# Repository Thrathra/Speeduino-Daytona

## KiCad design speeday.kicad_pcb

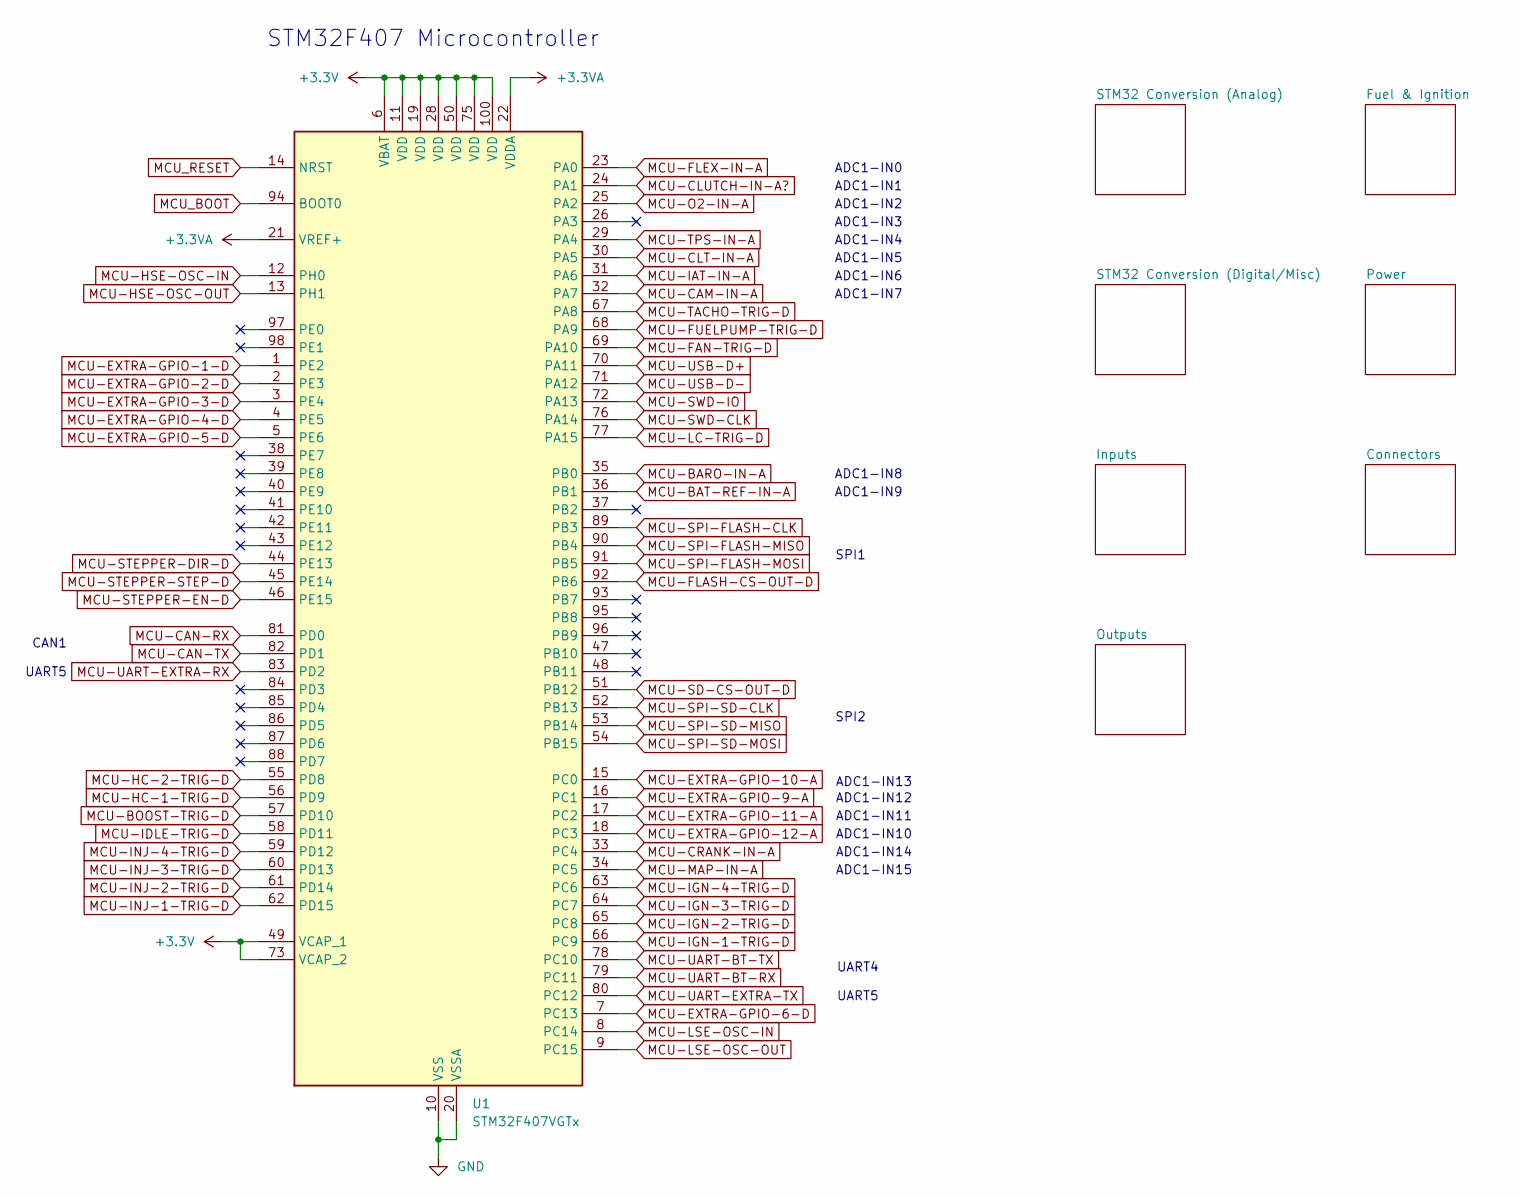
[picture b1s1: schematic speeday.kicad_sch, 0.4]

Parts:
U1: STM32F407VGTx; LQFP-100_14x14mm_P0.5mm

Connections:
+3.3V: U1.6 (VBAT), U1.11 (VDD), U1.19 (VDD), U1.28 (VDD), U1.49 (VCAP_1), U1.50 (VDD), U1.73 (VCAP_2), U1.75 (VDD), U1.100 (VDD); also elsewhere on the board
+3.3VA: U1.21 (VREF+), U1.22 (VDDA); also elsewhere on the board
GND: U1.10 (VSS), U1.20 (VSSA), U1.27 (VSS), U1.74 (VSS), U1.99 (VSS); also elsewhere on the board
MCU-BARO-IN-A: U1.35 (PB0); also elsewhere on the board
MCU-BAT-REF-IN-A: U1.36 (PB1); also elsewhere on the board
MCU-BOOST-TRIG-D: U1.57 (PD10); also elsewhere on the board
MCU-CAM-IN-A: U1.32 (PA7); also elsewhere on the board
MCU-CAN-RX: U1.81 (PD0); also elsewhere on the board
MCU-CAN-TX: U1.82 (PD1); also elsewhere on the board
MCU-CLT-IN-A: U1.30 (PA5); also elsewhere on the board
MCU-CLUTCH-IN-A?: U1.24 (PA1); also elsewhere on the board
MCU-CRANK-IN-A: U1.33 (PC4); also elsewhere on the board
MCU-EXTRA-GPIO-1-D: U1.1 (PE2); also elsewhere on the board
MCU-EXTRA-GPIO-2-D: U1.2 (PE3); also elsewhere on the board
MCU-EXTRA-GPIO-3-D: U1.3 (PE4); also elsewhere on the board
MCU-EXTRA-GPIO-4-D: U1.4 (PE5); also elsewhere on the board
MCU-EXTRA-GPIO-5-D: U1.5 (PE6); also elsewhere on the board
MCU-EXTRA-GPIO-6-D: U1.7 (PC13); also elsewhere on the board
MCU-EXTRA-GPIO-9-A: U1.16 (PC1); also elsewhere on the board
MCU-EXTRA-GPIO-10-A: U1.15 (PC0); also elsewhere on the board
MCU-EXTRA-GPIO-11-A: U1.17 (PC2); also elsewhere on the board
MCU-EXTRA-GPIO-12-A: U1.18 (PC3); also elsewhere on the board
MCU-FAN-TRIG-D: U1.69 (PA10); also elsewhere on the board
MCU-FLASH-CS-OUT-D: U1.92 (PB6); also elsewhere on the board
MCU-FLEX-IN-A: U1.23 (PA0); also elsewhere on the board
MCU-FUELPUMP-TRIG-D: U1.68 (PA9); also elsewhere on the board
MCU-HC-1-TRIG-D: U1.56 (PD9); also elsewhere on the board
MCU-HC-2-TRIG-D: U1.55 (PD8); also elsewhere on the board
MCU-HSE-OSC-IN: U1.12 (PH0); also elsewhere on the board
MCU-HSE-OSC-OUT: U1.13 (PH1); also elsewhere on the board
MCU-IAT-IN-A: U1.31 (PA6); also elsewhere on the board
MCU-IDLE-TRIG-D: U1.58 (PD11); also elsewhere on the board
MCU-IGN-1-TRIG-D: U1.66 (PC9); also elsewhere on the board
MCU-IGN-2-TRIG-D: U1.65 (PC8); also elsewhere on the board
MCU-IGN-3-TRIG-D: U1.64 (PC7); also elsewhere on the board
MCU-IGN-4-TRIG-D: U1.63 (PC6); also elsewhere on the board
MCU-INJ-1-TRIG-D: U1.62 (PD15); also elsewhere on the board
MCU-INJ-2-TRIG-D: U1.61 (PD14); also elsewhere on the board
MCU-INJ-3-TRIG-D: U1.60 (PD13); also elsewhere on the board
MCU-INJ-4-TRIG-D: U1.59 (PD12); also elsewhere on the board
MCU-LC-TRIG-D: U1.77 (PA15); also elsewhere on the board
MCU-LSE-OSC-IN: U1.8 (PC14); also elsewhere on the board
MCU-LSE-OSC-OUT: U1.9 (PC15); also elsewhere on the board
MCU-MAP-IN-A: U1.34 (PC5); also elsewhere on the board
MCU-O2-IN-A: U1.25 (PA2); also elsewhere on the board
MCU-SD-CS-OUT-D: U1.51 (PB12); also elsewhere on the board
MCU-SPI-FLASH-CLK: U1.89 (PB3); also elsewhere on the board
MCU-SPI-FLASH-MISO: U1.90 (PB4); also elsewhere on the board
MCU-SPI-FLASH-MOSI: U1.91 (PB5); also elsewhere on the board
MCU-SPI-SD-CLK: U1.52 (PB13); also elsewhere on the board
MCU-SPI-SD-MISO: U1.53 (PB14); also elsewhere on the board
MCU-SPI-SD-MOSI: U1.54 (PB15); also elsewhere on the board
MCU-STEPPER-DIR-D: U1.44 (PE13); also elsewhere on the board
MCU-STEPPER-EN-D: U1.46 (PE15); also elsewhere on the board
MCU-STEPPER-STEP-D: U1.45 (PE14); also elsewhere on the board
MCU-SWD-CLK: U1.76 (PA14); also elsewhere on the board
MCU-SWD-IO: U1.72 (PA13); also elsewhere on the board
MCU-TACHO-TRIG-D: U1.67 (PA8); also elsewhere on the board
MCU-TPS-IN-A: U1.29 (PA4); also elsewhere on the board
MCU-UART-BT-RX: U1.79 (PC11); also elsewhere on the board
MCU-UART-BT-TX: U1.78 (PC10); also elsewhere on the board
MCU-UART-EXTRA-RX: U1.83 (PD2); also elsewhere on the board
MCU-UART-EXTRA-TX: U1.80 (PC12); also elsewhere on the board
MCU-USB-D+: U1.70 (PA11); also elsewhere on the board
MCU-USB-D-: U1.71 (PA12); also elsewhere on the board
MCU_BOOT: U1.94 (BOOT0); also elsewhere on the board
MCU_RESET: U1.14 (NRST); also elsewhere on the board

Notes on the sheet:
SPI1
ADC1-IN3
CAN1
ADC1-IN14
ADC1-IN2
ADC1-IN5
UART5
ADC1-IN9
ADC1-IN13
ADC1-IN10
SPI2
ADC1-IN15
ADC1-IN8
ADC1-IN0
STM32F407 Microcontroller
UART4
ADC1-IN4
ADC1-IN7
ADC1-IN1
ADC1-IN12
ADC1-IN11
ADC1-IN6

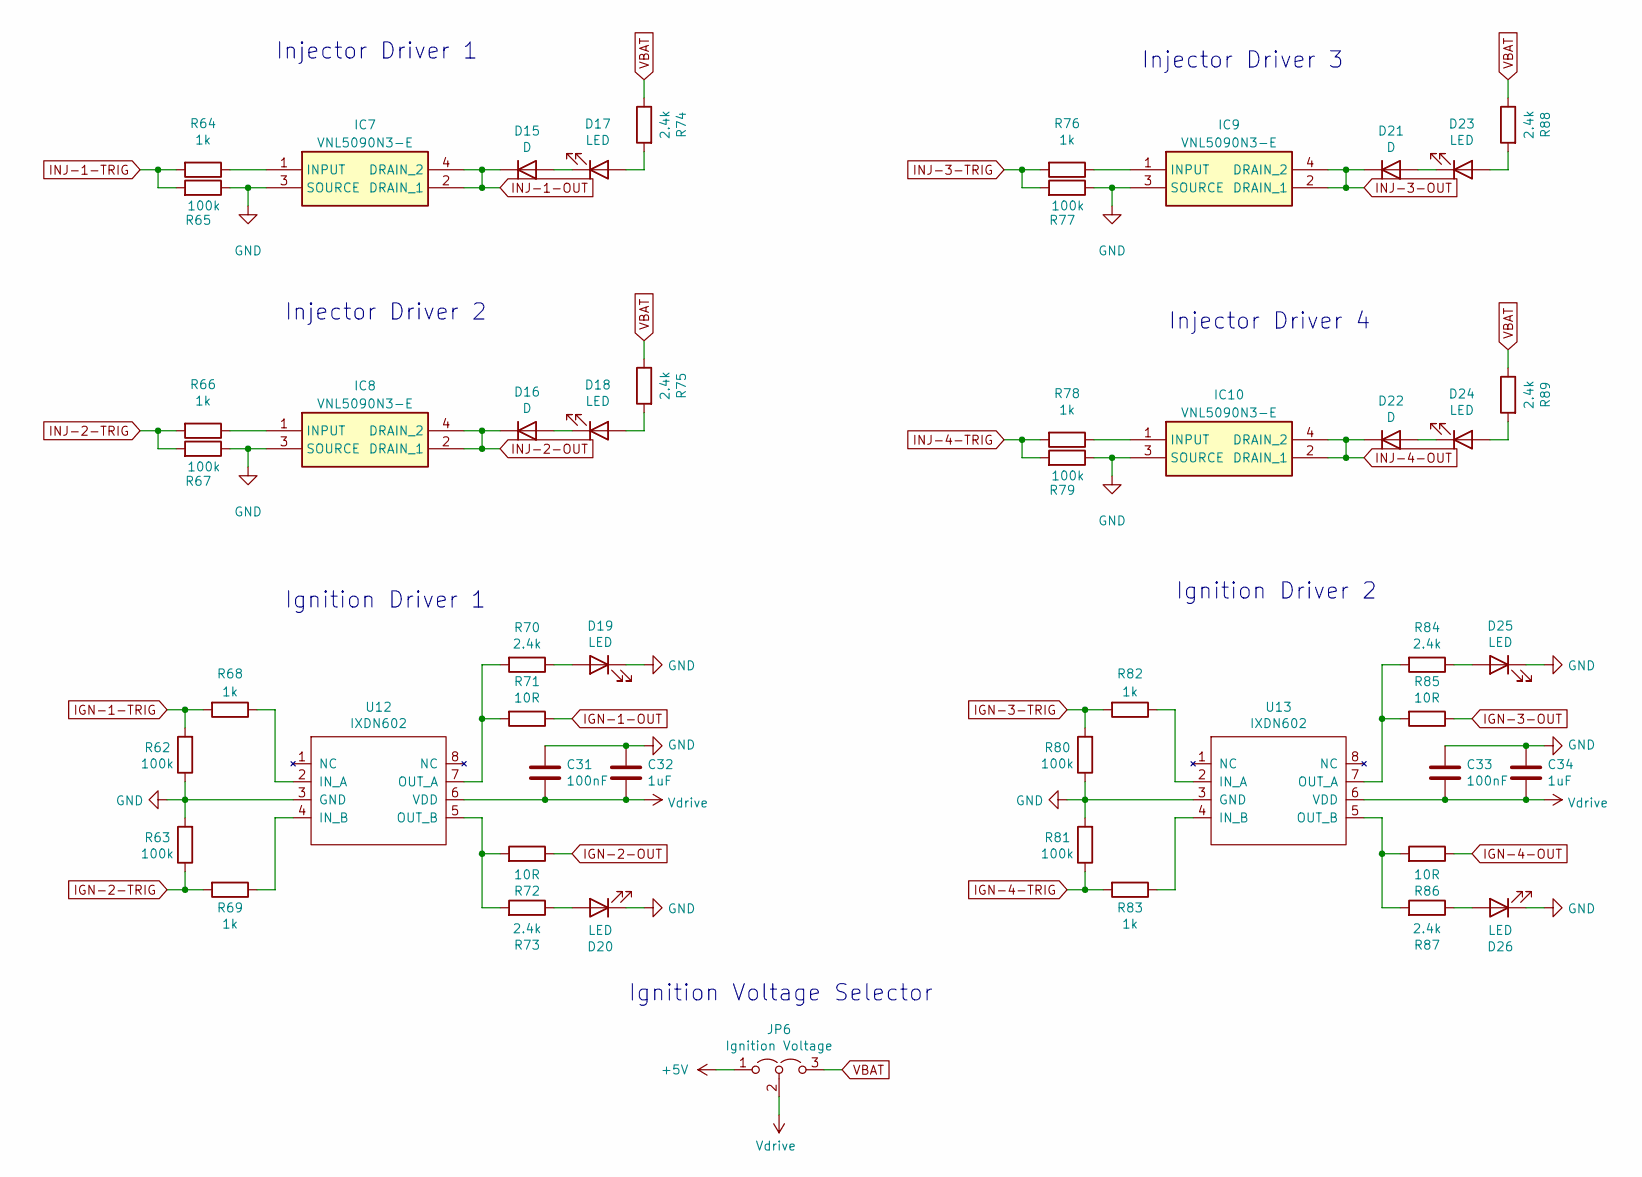
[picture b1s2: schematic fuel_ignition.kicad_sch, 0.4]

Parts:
C31, C33: 100nF; C_0805_2012Metric; Manufacturer_Part_Number CC0805KRX7R9BB104; Digikey Part Number 311-1140-1-ND
C32, C34: 1uF; C_0805_2012Metric; Manufacturer_Part_Number CC0805KKX7R7BB105; Digikey Part Number 311-1365-1-ND
D15, D16, D21, D22: D; D_SOD-323; Manufacturer_Part_Number 1N4448WX-TP; Digikey Part Number 1N4448WXTPMSCT-ND
D17, D18, D19, D20, D23, D24, D25, D26: LED; LED_0805_2012Metric; Manufacturer_Part_Number LH R974-LP-1; Digikey Part Number 475-1415-1-ND
IC7, IC8, IC9, IC10: VNL5090N3-E; SOT230P700X180-4N; Manufacturer_Part_Number VNL5090N3-E
JP6: Ignition Voltage; SolderJumper-3_P1.3mm_Open_RoundedPad1.0x1.5mm; Manufacturer_Part_Number M20-9990345; Digikey Part Number 952-2263-ND
R62, R63, R65, R67, R77, R79, R80, R81: 100k; R_0805_2012Metric; Manufacturer_Part_Number RC0805FR-07100KL; Digikey Part Number 311-100KCRCT-ND
R64, R66, R68, R69, R76, R78, R82, R83: 1k; R_0805_2012Metric; Manufacturer_Part_Number RC0805FR-071KL; Digikey Part Number 311-1.00KCRCT-ND
R70, R73, R74, R75, R84, R87, R88, R89: 2.4k; R_0805_2012Metric; Manufacturer_Part_Number RC0805FR-072K4L; Digikey Part Number 311-2.40KCRCT-ND
R71, R72, R85, R86: 10R; R_1206_3216Metric; Manufacturer_Part_Number RC1206FR-0710RL; Digikey Part Number 311-10.0FRCT-ND
U12, U13: IXDN602; SOIC-8_3.9x4.9mm_P1.27mm; Manufacturer_Part_Number IXDN602SIATR; Digikey Part Number 212-IXDN602SIACT-ND

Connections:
+5V: JP6.1 (A); also elsewhere on the board
GND: C31.1, C32.1, C33.1, C34.1, D19.1 (K), D20.1 (K), D25.1 (K), D26.1 (K), IC7.3 (SOURCE), IC8.3 (SOURCE), IC9.3 (SOURCE), IC10.3 (SOURCE), R62.1, R63.2, R65.1, R67.1, R77.1, R79.1, R80.1, R81.2, U12.3 (GND), U13.3 (GND); also elsewhere on the board
IGN-1-OUT: R71.1; also elsewhere on the board
IGN-1-TRIG: R62.2, R68.2; also elsewhere on the board
IGN-2-OUT: R72.1; also elsewhere on the board
IGN-2-TRIG: R63.1, R69.2; also elsewhere on the board
IGN-3-OUT: R85.1; also elsewhere on the board
IGN-3-TRIG: R80.2, R82.2; also elsewhere on the board
IGN-4-OUT: R86.1; also elsewhere on the board
IGN-4-TRIG: R81.1, R83.2; also elsewhere on the board
INJ-1-OUT: D15.1 (K), IC7.2 (DRAIN_1), IC7.4 (DRAIN_2); also elsewhere on the board
INJ-1-TRIG: R64.2, R65.2; also elsewhere on the board
INJ-2-OUT: D16.1 (K), IC8.2 (DRAIN_1), IC8.4 (DRAIN_2); also elsewhere on the board
INJ-2-TRIG: R66.2, R67.2; also elsewhere on the board
INJ-3-OUT: D21.1 (K), IC9.2 (DRAIN_1), IC9.4 (DRAIN_2); also elsewhere on the board
INJ-3-TRIG: R76.2, R77.2; also elsewhere on the board
INJ-4-OUT: D22.1 (K), IC10.2 (DRAIN_1), IC10.4 (DRAIN_2); also elsewhere on the board
INJ-4-TRIG: R78.2, R79.2; also elsewhere on the board
unnamed: D15.2 (A), D17.1 (K)
unnamed: D16.2 (A), D18.1 (K)
unnamed: D17.2 (A), R74.2
unnamed: D18.2 (A), R75.2
unnamed: D19.2 (A), R70.1
unnamed: D20.2 (A), R73.1
unnamed: D21.2 (A), D23.1 (K)
unnamed: D22.2 (A), D24.1 (K)
unnamed: D23.2 (A), R88.2
unnamed: D24.2 (A), R89.2
unnamed: D25.2 (A), R84.1
unnamed: D26.2 (A), R87.1
unnamed: IC7.1 (INPUT), R64.1
unnamed: IC8.1 (INPUT), R66.1
unnamed: IC9.1 (INPUT), R76.1
unnamed: IC10.1 (INPUT), R78.1
unnamed: R68.1, U12.2 (IN_A)
unnamed: R69.1, U12.4 (IN_B)
unnamed: R70.2, R71.2, U12.7 (OUT_A)
unnamed: R72.2, R73.2, U12.5 (OUT_B)
unnamed: R82.1, U13.2 (IN_A)
unnamed: R83.1, U13.4 (IN_B)
unnamed: R84.2, R85.2, U13.7 (OUT_A)
unnamed: R86.2, R87.2, U13.5 (OUT_B)
VBAT: JP6.3 (B), R74.1, R75.1, R88.1, R89.1; also elsewhere on the board
Vdrive: C31.2, C32.2, C33.2, C34.2, JP6.2 (C), U12.6 (VDD), U13.6 (VDD)

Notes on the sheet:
Ignition Voltage Selector
Injector Driver 4
Injector Driver 2
Ignition Driver 2
Injector Driver 1
Injector Driver 3
Ignition Driver 1

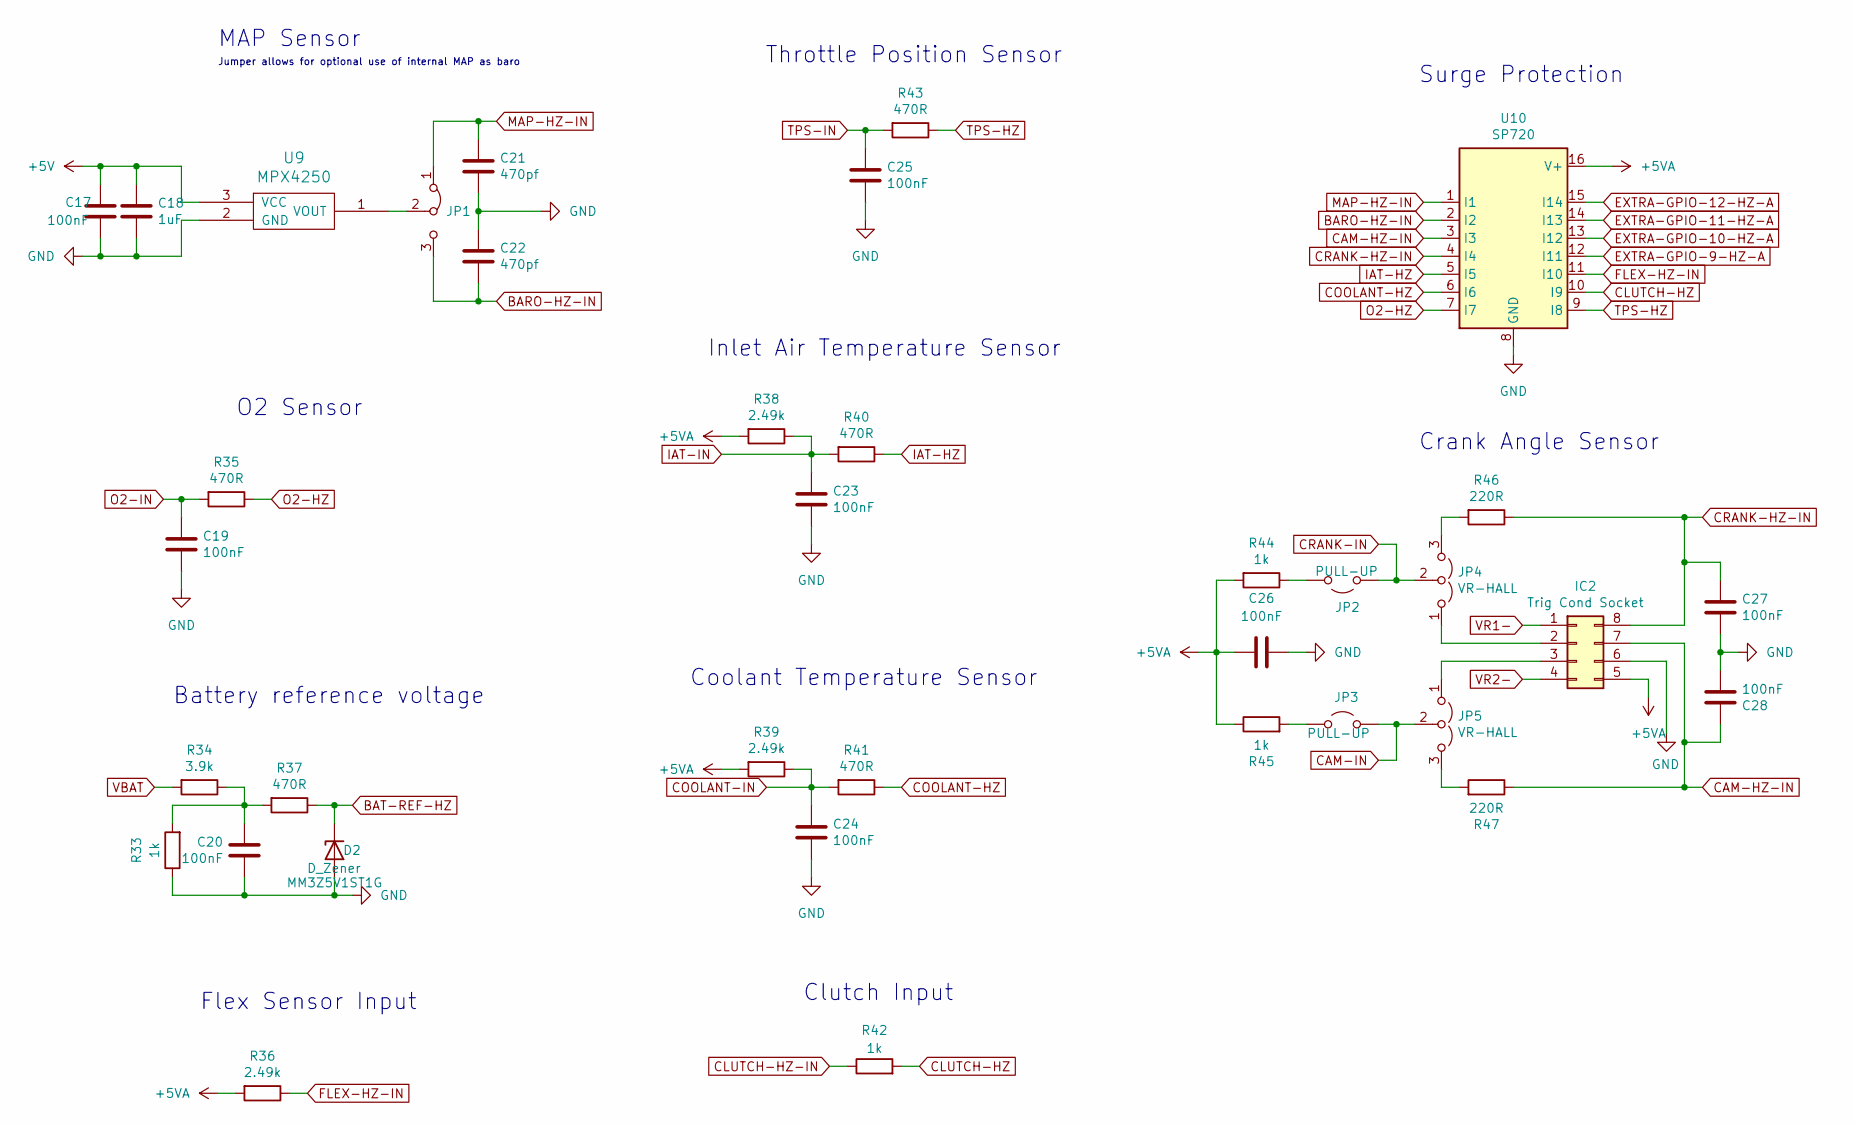
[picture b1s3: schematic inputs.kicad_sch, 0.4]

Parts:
C17, C27: 100nF; C_0805_2012Metric; Manufacturer_Part_Number CC0805KRX7R9BB103; Digikey Part Number 311-1136-1-ND
C18: 1uF; C_0805_2012Metric; Manufacturer_Part_Number CC0805KKX7R7BB105; Digikey Part Number 311-1365-1-ND
C19, C20, C23, C24, C25, C28: 100nF; C_0805_2012Metric; Manufacturer_Part_Number CC0805KRX7R9BB104; Digikey Part Number 311-1140-1-ND
C21, C22: 470pf; C_0805_2012Metric; Manufacturer_Part_Number CC0805KRX7R9BB471; Digikey Part Number 311-1124-1-ND
C26: 100nF; C_0805_2012Metric
D2: D_Zener; D_SOD-323; Part # MM3Z5V1ST1G; Digikey Part Number MM3Z5V1ST1GOSCT-ND
IC2: Trig Cond Socket; DIP-8_W7.62mm_Socket
JP1: Jumper_3_Bridged12; SolderJumper-3_P1.3mm_Open_RoundedPad1.0x1.5mm
JP2, JP3: PULL-UP; SolderJumper-2_P1.3mm_Open_RoundedPad1.0x1.5mm; Manufacturer_Part_Number M20-9990245; Digikey Part Number 952-2261-ND
JP4, JP5: VR-HALL; SolderJumper-3_P1.3mm_Open_RoundedPad1.0x1.5mm; Manufacturer_Part_Number M20-9990345; Digikey Part Number 952-2263-ND
R33, R42, R44, R45: 1k; R_0805_2012Metric; Manufacturer_Part_Number RC0805FR-071KL; Digikey Part Number 311-1.00KCRCT-ND
R34: 3.9k; R_0805_2012Metric; Manufacturer_Part_Number RC0805FR-073K9L; Digikey Part Number 311-3.90KCRCT-ND
R35, R37, R40, R41, R43: 470R; R_0805_2012Metric; Manufacturer_Part_Number ERJ-6ENF4700V; Digikey Part Number P470CCT-ND
R36: 2.49k; R_0805_2012Metric; Manufacturer_Part_Number RC0805FR-072K4L; Digikey Part Number 311-2.40KCRCT-ND
R38, R39: 2.49k; R_0805_2012Metric; Manufacturer_Part_Number RT0805BRD072K49L; Digikey Part Number YAG1854CT-ND
R46, R47: 220R; R_0805_2012Metric; Manufacturer_Part_Number RC0805FR-07220RL; Digikey Part Number 311-220CRCT-ND
U9: MPX4250; Manufacturer_Part_Number MPX4250AP; Digikey Part Number MPX4250AP-ND
U10: SP720; SOIC-16_3.9x9.9mm_P1.27mm; Manufacturer_Part_Number SP720ABTG; Digikey Part Number F3162CT-ND

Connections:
+5V: C17.1, C18.1, U9.3 (VCC); also elsewhere on the board
+5VA: C26.1, IC2.5, R36.2, R38.2, R39.2, R44.2, R45.1, U10.16 (V+); also elsewhere on the board
BARO-HZ-IN: C22.2, JP1.3 (B), U10.2 (I2); also elsewhere on the board
BAT-REF-HZ: D2.1 (K), R37.1; also elsewhere on the board
CAM-HZ-IN: C28.1, IC2.7, R47.1, U10.3 (I3); also elsewhere on the board
CAM-IN: JP3.2 (B), JP5.2 (C); also elsewhere on the board
CLUTCH-HZ: R42.2, U10.10 (I9); also elsewhere on the board
CLUTCH-HZ-IN: R42.1; also elsewhere on the board
COOLANT-HZ: R41.1, U10.6 (I6); also elsewhere on the board
COOLANT-IN: C24.1, R39.1, R41.2; also elsewhere on the board
CRANK-HZ-IN: C27.1, IC2.8, R46.1, U10.4 (I4); also elsewhere on the board
CRANK-IN: JP2.1 (A), JP4.2 (C); also elsewhere on the board
EXTRA-GPIO-9-HZ-A: U10.12 (I11); also elsewhere on the board
EXTRA-GPIO-10-HZ-A: U10.13 (I12); also elsewhere on the board
EXTRA-GPIO-11-HZ-A: U10.14 (I13); also elsewhere on the board
EXTRA-GPIO-12-HZ-A: U10.15 (I14); also elsewhere on the board
FLEX-HZ-IN: R36.1, U10.11 (I10); also elsewhere on the board
GND: C17.2, C18.2, C19.2, C20.2, C21.2, C22.1, C23.2, C24.2, C25.2, C26.2, C27.2, C28.2, D2.2 (A), IC2.6, R33.1, U9.2 (GND), U10.8 (GND); also elsewhere on the board
IAT-HZ: R40.1, U10.5 (I5); also elsewhere on the board
IAT-IN: C23.1, R38.1, R40.2; also elsewhere on the board
MAP-HZ-IN: C21.1, JP1.1 (A), U10.1 (I1); also elsewhere on the board
unnamed: C20.1, R33.2, R34.1, R37.2
unnamed: IC2.2, JP4.1 (A)
unnamed: IC2.3, JP5.1 (A)
unnamed: JP1.2 (C), U9.1 (VOUT)
unnamed: JP2.2 (B), R44.1
unnamed: JP3.1 (A), R45.2
unnamed: JP4.3 (B), R46.2
unnamed: JP5.3 (B), R47.2
O2-HZ: R35.1, U10.7 (I7); also elsewhere on the board
O2-IN: C19.1, R35.2; also elsewhere on the board
TPS-HZ: R43.1, U10.9 (I8); also elsewhere on the board
TPS-IN: C25.1, R43.2; also elsewhere on the board
VBAT: R34.2; also elsewhere on the board
VR1-: IC2.1; also elsewhere on the board
VR2-: IC2.4; also elsewhere on the board

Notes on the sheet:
Jumper allows for optional use of internal MAP as baro
Crank Angle Sensor
Battery reference voltage
O2 Sensor
Inlet Air Temperature Sensor
Surge Protection
Throttle Position Sensor
Flex Sensor Input
Clutch Input
MAP Sensor
Coolant Temperature Sensor

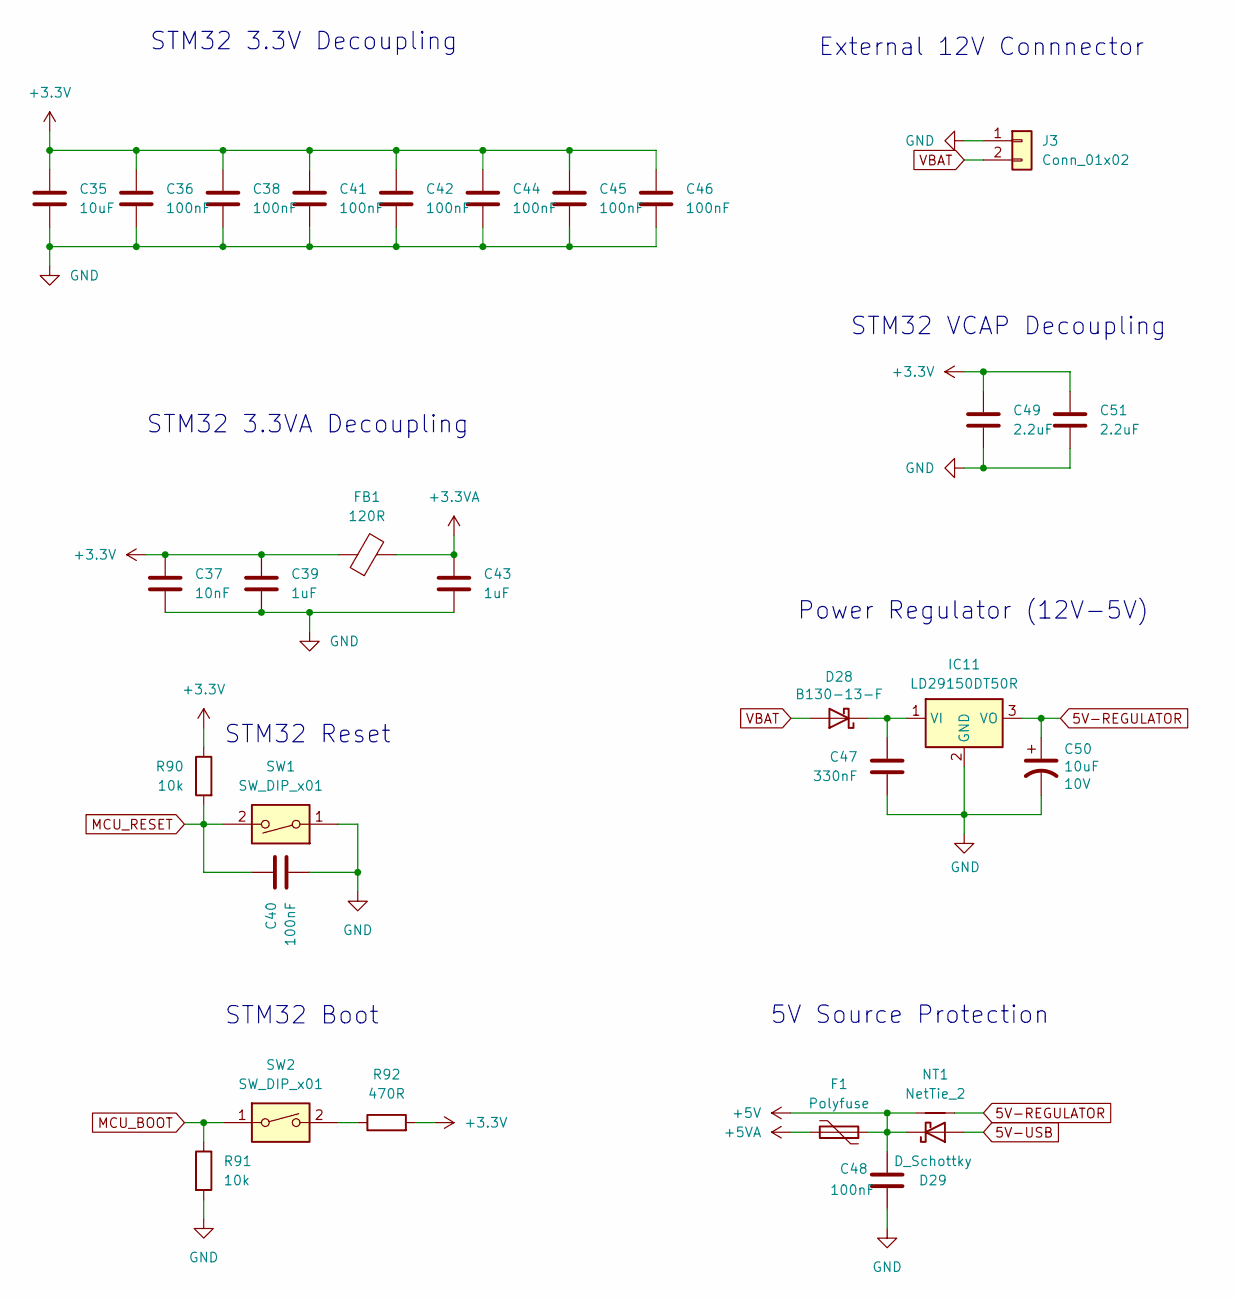
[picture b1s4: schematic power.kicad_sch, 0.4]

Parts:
C35: 10uF; C_0805_2012Metric
C36, C38, C40, C41, C42, C44, C45, C46: 100nF; C_0805_2012Metric
C37: 10nF; C_0805_2012Metric
C39, C43: 1uF; C_0805_2012Metric
C47: 330nF; C_0805_2012Metric; Voltage 25V
C48: 100nF; C_0805_2012Metric; Manufacturer_Part_Number CC0805KRX7R9BB104; Digikey Part Number 311-1140-1-ND
C49, C51: 2.2uF; C_0805_2012Metric
C50: 10uF; CP_EIA-3528-12_Kemet-T; Voltage 10V; Manufacturer_Part_Number TAJB476K006RNJ; Digikey Part Number 478-1692-1-ND
D28: B130-13-F; D_SMA; Manufacturer_Part_Number B130-13-F; Digikey Part Number B130-FDICT-ND
D29: D_Schottky; D_SOD-323
F1: Polyfuse; Fuse_1812_4532Metric
FB1: 120R; L_0805_2012Metric
IC11: LD29150DT50R; TO-252-2; Manufacturer_Part_Number LD29150DT50R; Mouser Part Number 511-LD29150DT50R
J3: Conn_01x02; AMASS_XT30U-F_1x02_P5.0mm_Vertical
NT1: NetTie_2; NetTie-2_SMD_Pad0.5mm
R90, R91: 10k; R_0805_2012Metric
R92: 470R; R_0805_2012Metric
SW1, SW2: SW_DIP_x01; SW_SPST_B3U-1000P

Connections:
5V-REGULATOR: C50.1, IC11.3 (VO), NT1.2
5V-USB: D29.2 (A); also elsewhere on the board
+3.3V: C35.1, C36.1, C37.1, C38.1, C39.1, C41.1, C42.1, C44.1, C45.1, C46.1, C49.1, C51.1, FB1.1, R90.1, R92.2; also elsewhere on the board
+3.3VA: C43.1, FB1.2; also elsewhere on the board
+5V: C48.1, D29.1 (K), F1.1, NT1.1; also elsewhere on the board
+5VA: F1.2; also elsewhere on the board
GND: C35.2, C36.2, C37.2, C38.2, C39.2, C40.2, C41.2, C42.2, C43.2, C44.2, C45.2, C46.2, C47.2, C48.2, C49.2, C50.2, C51.2, IC11.2 (GND), J3.1, R91.2, SW1.1; also elsewhere on the board
MCU_BOOT: R91.1, SW2.1; also elsewhere on the board
MCU_RESET: C40.1, R90.2, SW1.2; also elsewhere on the board
unnamed: C47.1, D28.1 (K), IC11.1 (VI)
unnamed: R92.1, SW2.2
VBAT: D28.2 (A), J3.2; also elsewhere on the board

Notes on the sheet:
5V Source Protection
STM32 3.3VA Decoupling
External 12V Connnector
STM32 VCAP Decoupling
STM32 3.3V Decoupling
Power Regulator (12V-5V)
STM32 Boot
STM32 Reset

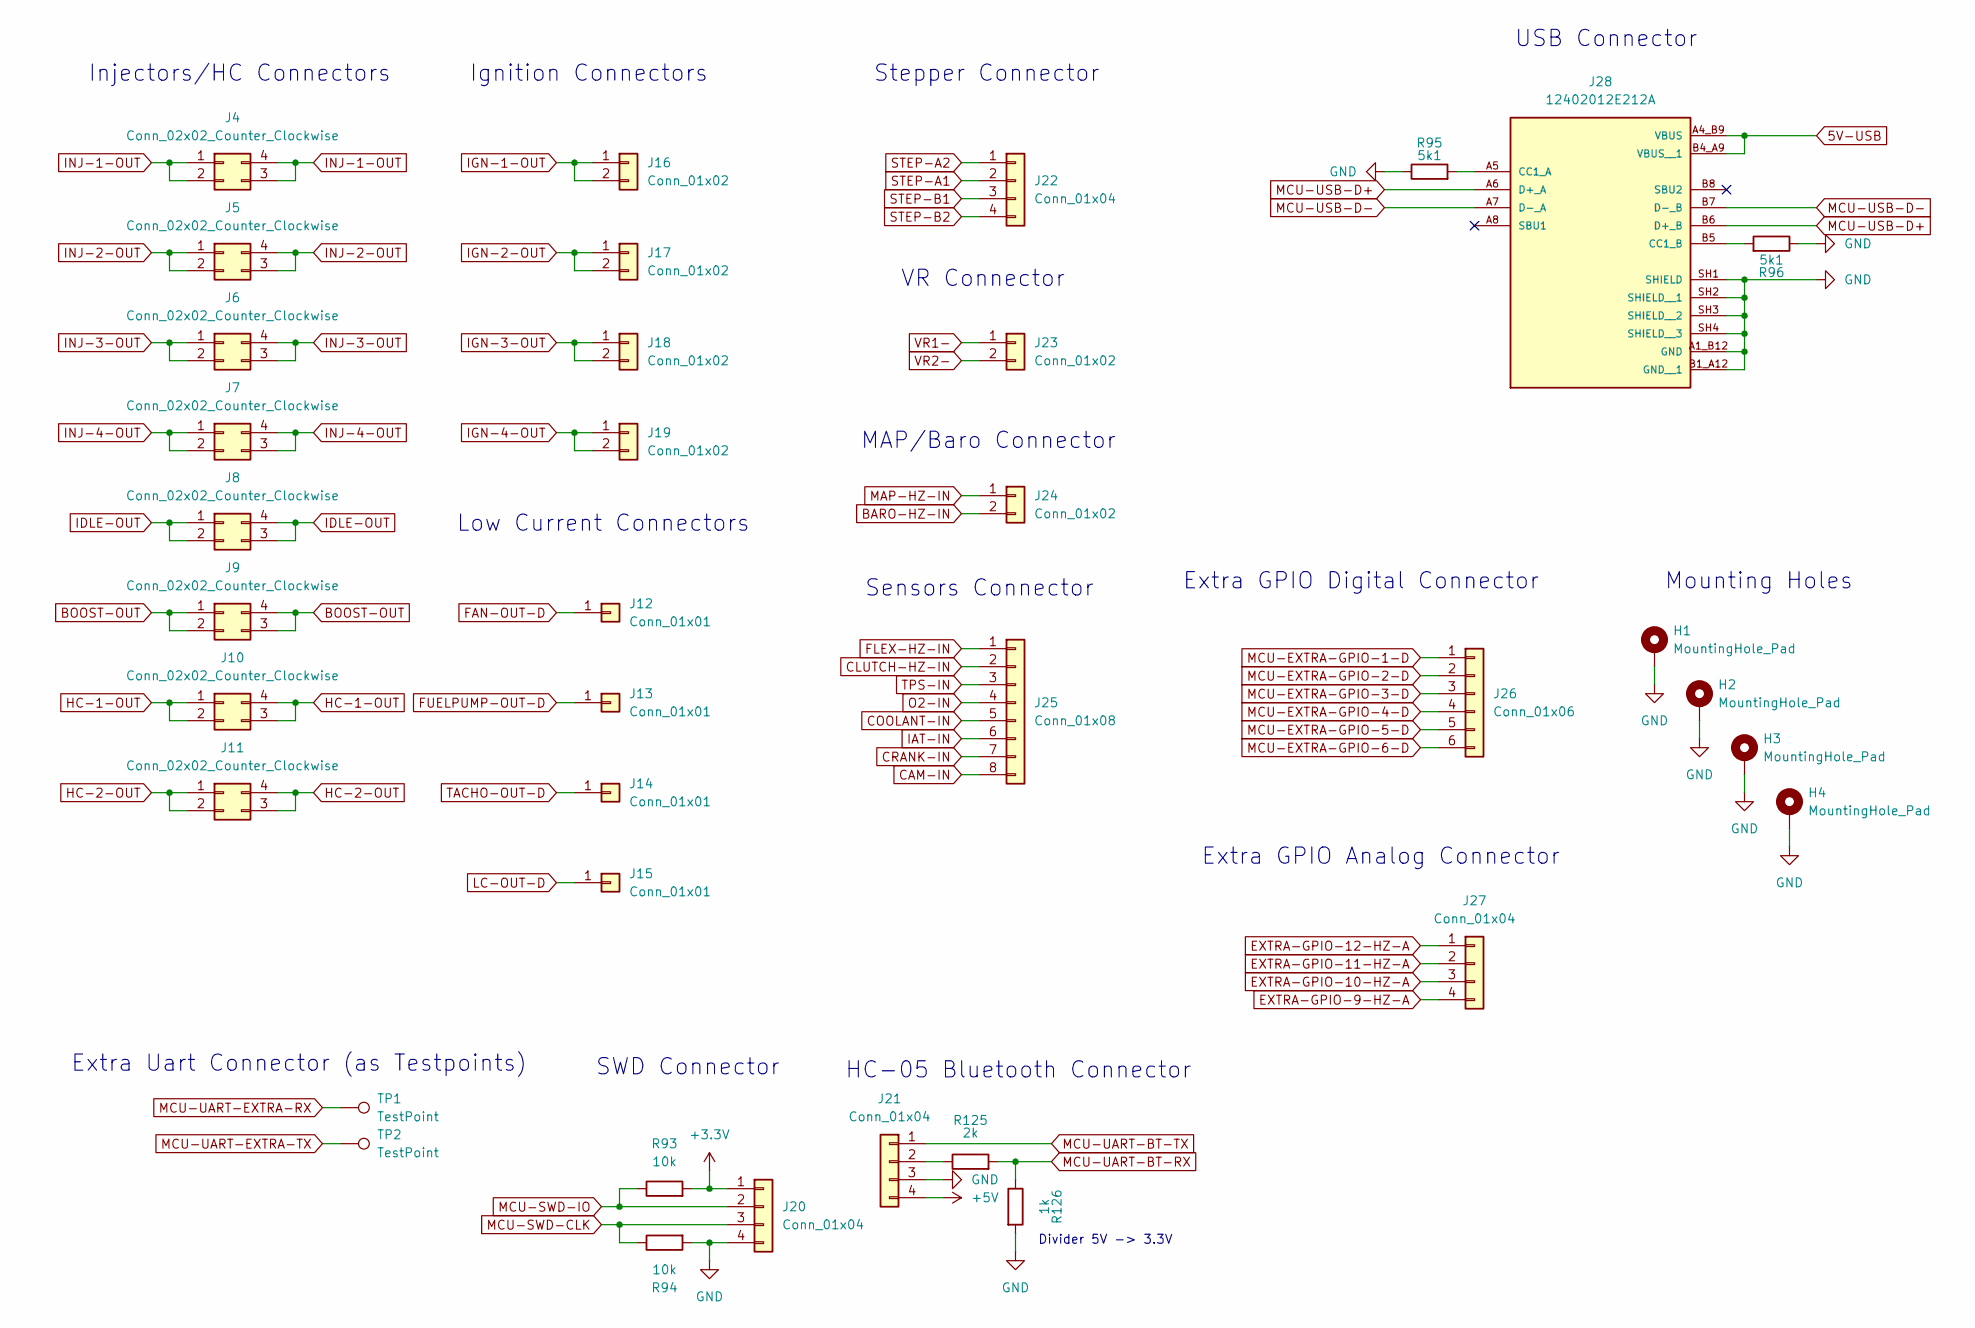
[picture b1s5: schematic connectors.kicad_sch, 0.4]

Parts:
H1, H2, H3, H4: MountingHole_Pad; MountingHole_4mm_Pad
J4, J5, J6, J7, J8, J9, J10, J11: Conn_02x02_Counter_Clockwise; PinHeader_2x02_P2.54mm_Vertical
J12, J13, J14, J15: Conn_01x01; PinHeader_1x01_P2.54mm_Vertical
J16, J17, J18, J19, J23, J24: Conn_01x02; PinHeader_1x02_P2.54mm_Vertical
J20, J21, J22, J27: Conn_01x04; PinHeader_1x04_P2.54mm_Vertical
J25: Conn_01x08; PinHeader_1x08_P2.54mm_Vertical
J26: Conn_01x06; PinHeader_1x06_P2.54mm_Vertical
J28: 12402012E212A; AMPHENOL_12402012E212A; PARTREV 4
R93, R94: 10k; R_0805_2012Metric
R95, R96: 5k1; R_0805_2012Metric
R125: 2k; R_0805_2012Metric
R126: 1k; R_0805_2012Metric
TP1, TP2: TestPoint; TestPoint_Pad_D1.0mm

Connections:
5V-USB: J28.A4_B9 (VBUS), J28.B4_A9 (VBUS__1); also elsewhere on the board
+3.3V: J20.1, R93.2; also elsewhere on the board
+5V: J21.4; also elsewhere on the board
BARO-HZ-IN: J24.2; also elsewhere on the board
BOOST-OUT: J9.1, J9.2, J9.3, J9.4; also elsewhere on the board
CAM-IN: J25.8; also elsewhere on the board
CLUTCH-HZ-IN: J25.2; also elsewhere on the board
COOLANT-IN: J25.5; also elsewhere on the board
CRANK-IN: J25.7; also elsewhere on the board
EXTRA-GPIO-9-HZ-A: J27.4; also elsewhere on the board
EXTRA-GPIO-10-HZ-A: J27.3; also elsewhere on the board
EXTRA-GPIO-11-HZ-A: J27.2; also elsewhere on the board
EXTRA-GPIO-12-HZ-A: J27.1; also elsewhere on the board
FAN-OUT-D: J12.1 (Pin_1_1); also elsewhere on the board
FLEX-HZ-IN: J25.1; also elsewhere on the board
FUELPUMP-OUT-D: J13.1 (Pin_1_1); also elsewhere on the board
GND: H1.1 (1_1), H2.1 (1_1), H3.1 (1_1), H4.1 (1_1), J20.4, J21.3, J28.A1_B12 (GND), J28.B1_A12 (GND__1), J28.SH1 (SHIELD), J28.SH2 (SHIELD__1), J28.SH3 (SHIELD__2), J28.SH4 (SHIELD__3), R94.2, R95.1, R96.1, R126.2; also elsewhere on the board
HC-1-OUT: J10.1, J10.2, J10.3, J10.4; also elsewhere on the board
HC-2-OUT: J11.1, J11.2, J11.3, J11.4; also elsewhere on the board
IAT-IN: J25.6; also elsewhere on the board
IDLE-OUT: J8.1, J8.2, J8.3, J8.4; also elsewhere on the board
IGN-1-OUT: J16.1, J16.2; also elsewhere on the board
IGN-2-OUT: J17.1, J17.2; also elsewhere on the board
IGN-3-OUT: J18.1, J18.2; also elsewhere on the board
IGN-4-OUT: J19.1, J19.2; also elsewhere on the board
INJ-1-OUT: J4.1, J4.2, J4.3, J4.4; also elsewhere on the board
INJ-2-OUT: J5.1, J5.2, J5.3, J5.4; also elsewhere on the board
INJ-3-OUT: J6.1, J6.2, J6.3, J6.4; also elsewhere on the board
INJ-4-OUT: J7.1, J7.2, J7.3, J7.4; also elsewhere on the board
LC-OUT-D: J15.1 (Pin_1_1); also elsewhere on the board
MAP-HZ-IN: J24.1; also elsewhere on the board
MCU-EXTRA-GPIO-1-D: J26.1; also elsewhere on the board
MCU-EXTRA-GPIO-2-D: J26.2; also elsewhere on the board
MCU-EXTRA-GPIO-3-D: J26.3; also elsewhere on the board
MCU-EXTRA-GPIO-4-D: J26.4; also elsewhere on the board
MCU-EXTRA-GPIO-5-D: J26.5; also elsewhere on the board
MCU-EXTRA-GPIO-6-D: J26.6; also elsewhere on the board
MCU-SWD-CLK: J20.3, R94.1; also elsewhere on the board
MCU-SWD-IO: J20.2, R93.1; also elsewhere on the board
MCU-UART-BT-RX: R125.2, R126.1; also elsewhere on the board
MCU-UART-BT-TX: J21.1; also elsewhere on the board
MCU-UART-EXTRA-RX: TP1.1 (1_1); also elsewhere on the board
MCU-UART-EXTRA-TX: TP2.1 (1_1); also elsewhere on the board
MCU-USB-D+: J28.A6 (D+_A), J28.B6 (D+_B); also elsewhere on the board
MCU-USB-D-: J28.A7 (D-_A), J28.B7 (D-_B); also elsewhere on the board
unnamed: J21.2, R125.1
unnamed: J28.A5 (CC1_A), R95.2
unnamed: J28.B5 (CC1_B), R96.2
O2-IN: J25.4; also elsewhere on the board
STEP-A1: J22.2; also elsewhere on the board
STEP-A2: J22.1; also elsewhere on the board
STEP-B1: J22.3; also elsewhere on the board
STEP-B2: J22.4; also elsewhere on the board
TACHO-OUT-D: J14.1 (Pin_1_1); also elsewhere on the board
TPS-IN: J25.3; also elsewhere on the board
VR1-: J23.1; also elsewhere on the board
VR2-: J23.2; also elsewhere on the board

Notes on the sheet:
Extra GPIO Analog Connector
Injectors/HC Connectors
Stepper Connector
Divider 5V -> 3.3V
Sensors Connector
VR Connector
Low Current Connectors
Extra GPIO Digital Connector
Mounting Holes
SWD Connector
MAP/Baro Connector
USB Connector
Ignition Connectors
Extra Uart Connector (as Testpoints)
HC-05 Bluetooth Connector
